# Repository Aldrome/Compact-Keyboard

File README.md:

# Compact Piano Keyboard with DSP and MIDI functions

Schematic link
https://drive.google.com/drive/folders/1MW6RK4cLdNylEYujYAkNW5wjjUnl7ojT?usp=drive_link

Most piano keyboards that musicians use are full scale, which causes problems for composing or playing
in places that lack the space or accessibility, since it is made for performance. This keyboard project has the
focus of minimizing size to something you can fit on a desk and be able to move more freely with it. It will be
more of a MIDI controller and music creation, not as a performance machine.

### Current Objective
	Aldrich: Code general functions and create midi function for 1-3 keys
 	Andrew:  Create a keyboard matrix (48 keys) [Search keyboard matrix for more info]

## Issues to think about:
	- Choosing a microcontroller with the DSP and MIDI capability (Using Teensy 4.1 + Audio Shield Rev D)
	- Handle the keyboard matrix and decide the key amount
	- PCB designing and how to route the I/Os
	- The type of inputs, considering it is a piano

## Planning with steps
	1. Prepare microcontroller for use (solder all pin feet in place)
	2. Test out audio I/O using only the headphones
	3. Prototype a simple synth wave maker using a few buttons
	4. If possible, use a synth wave synthesizer to create a piano sound, maybe more. Else, use audio from free source.
	5. Create a prototype keyboard matrix, and a full scale on KiCad. Also add anti-ghosting using diodes.
	6. Test out potentiometer to divide the input keys to 2 sections.
	7. Add a slider + button for DSP, similar to a mixer.
	8. Depending on the time constraint and resources, print a PCB to handle all these features.

## Additional feature that can be added, though not a priority
	1. A display with UI implementation to decide instrument or maybe change DSP settings.
	2. The input keys by default will be a simple button, similar to a typing keyboard.
	   But if possible, use a sensitivity keyboard using a 2 point detector.
	3. No casings for this project.

Notes: This project will be done in 2 parts for every steps that includes prototyping. One being the physical prototype and
       the other part being the schematic design. After finishing schematic, create a footprint for PCB. Printing a PCB will not
       be a priority, as the demo will mainly be a concept using a prototype. Though we will print a PCB if possible.

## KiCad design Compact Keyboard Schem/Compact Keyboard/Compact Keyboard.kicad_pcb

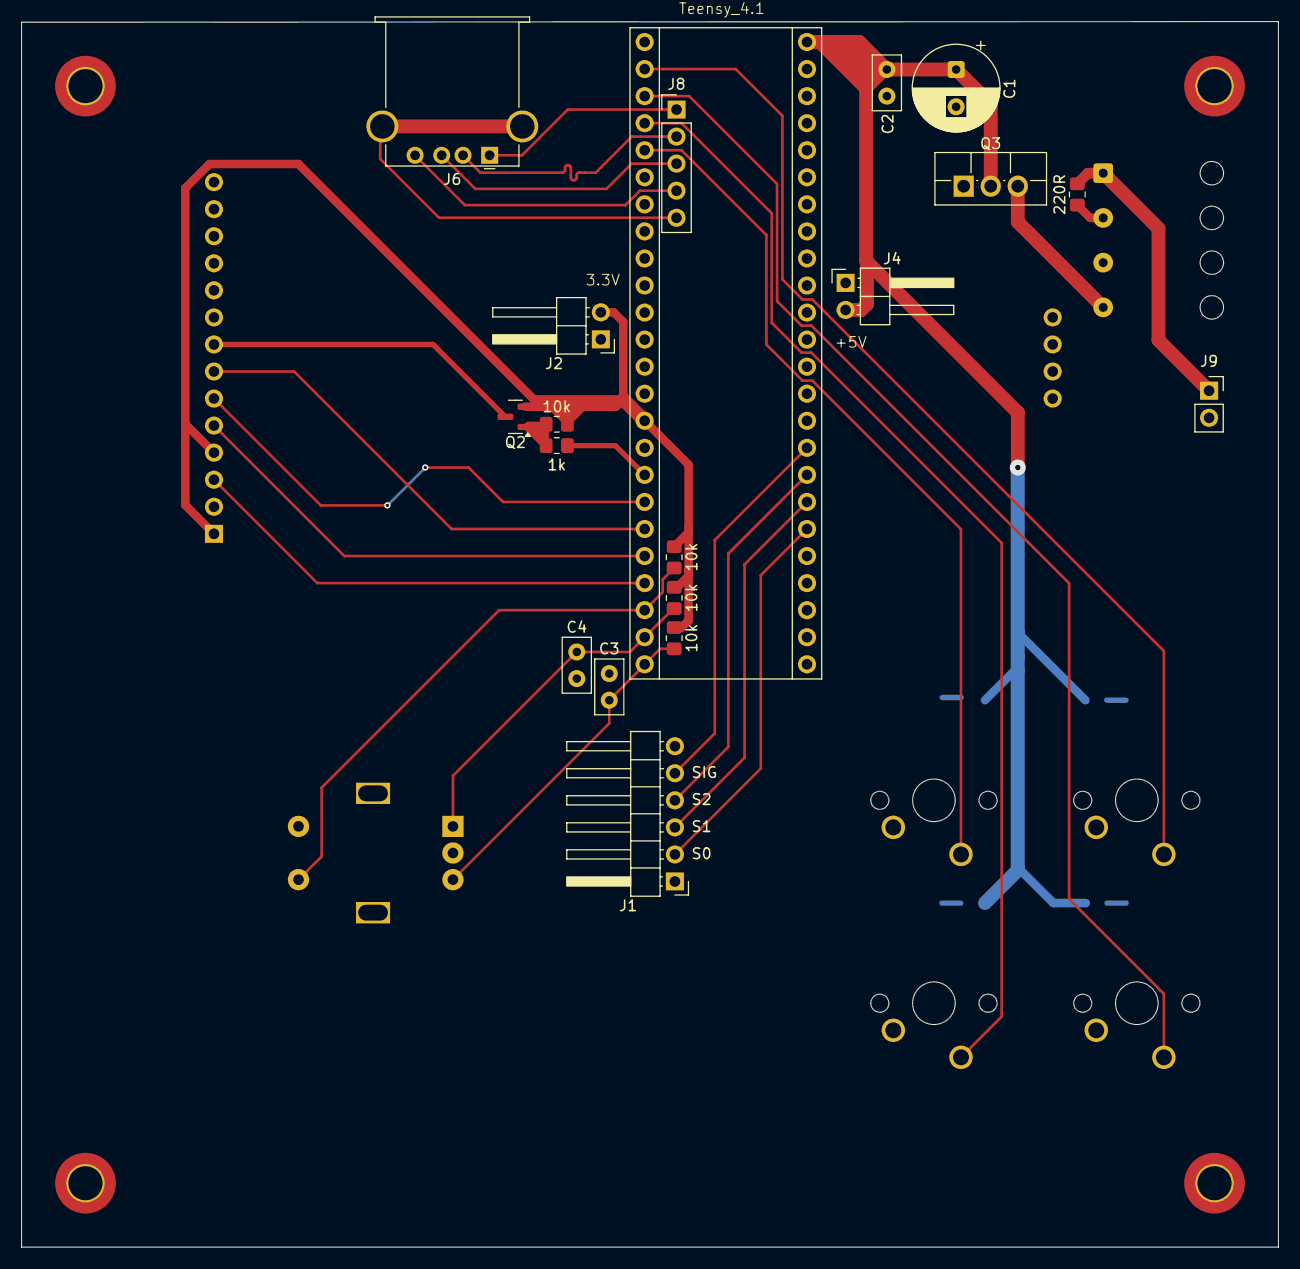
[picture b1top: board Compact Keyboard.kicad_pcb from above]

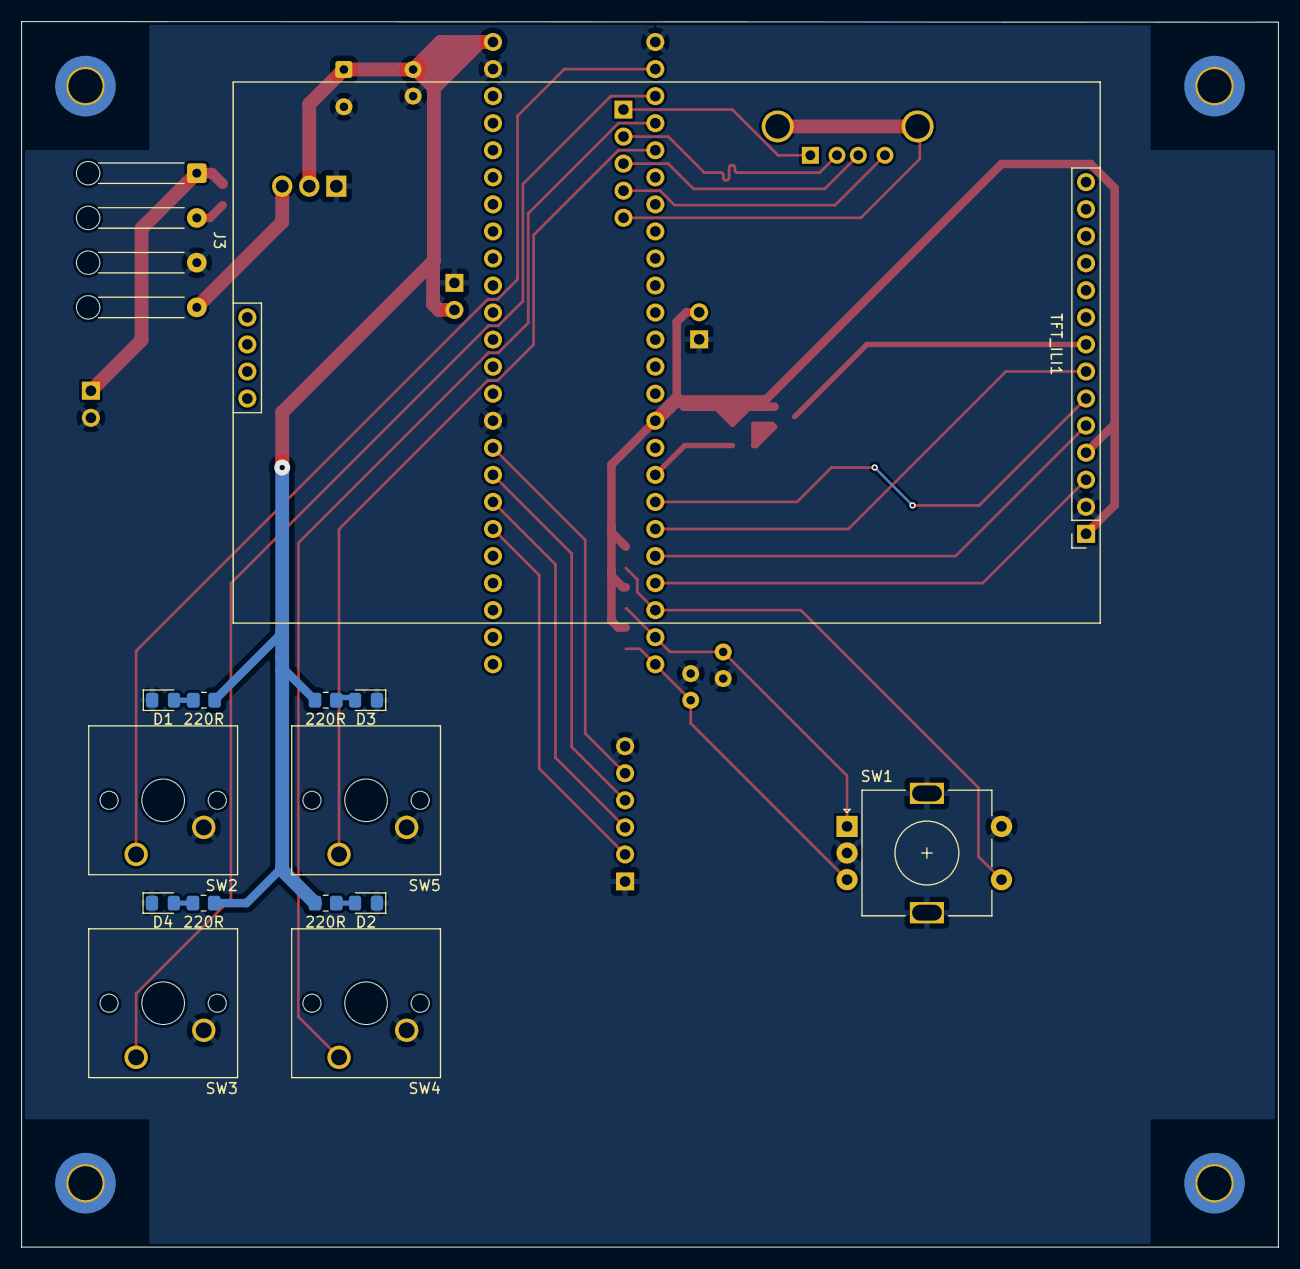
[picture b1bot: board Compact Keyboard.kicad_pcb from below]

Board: 2 copper layers, 118.0 x 115.1 mm, 34 parts (15 on the bottom side), 33 nets.

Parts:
1k: 1k; R_0805_2012Metric_Pad1.20x1.40mm_HandSolder
10k, 10k#2, 10k#4: 10K; R_0805_2012Metric_Pad1.20x1.40mm_HandSolder
10k#3: 10k; R_0805_2012Metric_Pad1.20x1.40mm_HandSolder
220R, 220R#2, 220R#3, 220R#4, 220R#5: 220R; R_0805_2012Metric_Pad1.20x1.40mm_HandSolder
C1: 470uF; CP_Radial_D8.0mm_P3.50mm
C2, C3, C4: 0.1uF; C_Disc_D5.0mm_W2.5mm_P2.50mm
D1, D2, D3, D4: LED; LED_0805_2012Metric_Pad1.15x1.40mm_HandSolder
J1: MUX+POT; PinHeader_1x06_P2.54mm_Horizontal
J2: MUX Power; PinHeader_1x02_P2.54mm_Horizontal
J3: SW_Switch_LED; SolderWire-0.25sqmm_1x04_P4.2mm_D0.65mm_OD1.7mm_Relief
J4: PAM8406 Power; PinHeader_1x02_P2.54mm_Horizontal
J6: USB_A; USB_A_Stewart_SS-52100-001_Horizontal
J8: USB_Host; PinHeader_1x05_P2.54mm_Vertical
J9: Jack-DC; PinSocket_1x02_P2.54mm_Vertical
Q2: Q_PMOS_GSD; SOT-23
Q3: Q_PMOS_GDS; TO-220F-3_Vertical
SW1: RotaryEncoder_Switch_MP; RotaryEncoder_Alps_EC11E-Switch_Vertical_H20mm
SW2, SW3, SW4, SW5: SW_Push; SW_Cherry_MX_1.00u_PCB
TFT_ILI1: ILI9341_TFT
Teensy_4.1: Teensy

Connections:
+3.3V: 10k.1, 10k#2.1, 10k#3.2, 10k#4.2, J2.2, Q2.2 (S), TFT_ILI1.1 (VCC), TFT_ILI1.4 (RESET), Teensy_4.1.15 (3.3V), Teensy_4.1.46 (3.3V)
+5V: 220R#2.2, 220R#3.2, 220R#4.2, 220R#5.2, C1.1, C2.1, J4.2, Q3.2 (D), Teensy_4.1.48 (Vin)
/Buttons/BTN1_IN: SW2.1, Teensy_4.1.2 (0)
/Buttons/BTN2_IN: SW3.1, Teensy_4.1.3 (1)
/Buttons/BTN3_IN: SW4.1, Teensy_4.1.4 (2)
/Buttons/BTN4_IN: SW5.1, Teensy_4.1.5 (3)
/D+_USB: J6.3 (D+), J8.3
/D-_USB: J6.2 (D-), J8.2
/GND_USB: J6.4 (GND), J8.4
/ILI_9341/CS_LCD: TFT_ILI1.3 (CS), Teensy_4.1.21 (29)
/ILI_9341/DC_LCD: TFT_ILI1.5 (DC), Teensy_4.1.20 (28)
/ILI_9341/LED_LCD: 1k.2, Teensy_4.1.17 (25)
/ILI_9341/MOSI_LCD: TFT_ILI1.6 (SDI(MOSI)), Teensy_4.1.18 (26)
/ILI_9341/SCK_LCD: TFT_ILI1.7 (SCK), Teensy_4.1.19 (27)
/Rotary_Encoder/CLK_RE: 10k.2, C3.1, SW1.B, Teensy_4.1.24 (32)
/Rotary_Encoder/DT_RE: 10k#2.2, C4.1, SW1.A, Teensy_4.1.23 (31)
/Rotary_Encoder/SW_RE: 10k#4.1, SW1.S1, Teensy_4.1.22 (30)
/S0_MUX: J1.2, Teensy_4.1.30 (38)
/S1_MUX: J1.3, Teensy_4.1.31 (39)
/S2_MUX: J1.4, Teensy_4.1.32 (40)
/SIG_MUX: J1.5, Teensy_4.1.33 (41)
/Shield_USB: J6.5 (Shield), J8.5
/VBUS_USB: J6.1 (VBUS), J8.1
GND: C1.2, C2.2, C3.2, C4.2, D1.1 (K), D2.1 (K), D3.1 (K), D4.1 (K), J1.1, J1.6, J2.1, J3.3, J4.1, J9.2, Q3.1 (G), SW1.C, SW1.MP, SW1.S2, SW2.2, SW3.2, SW4.2, SW5.2, TFT_ILI1.2 (GND), Teensy_4.1.1 (GND), Teensy_4.1.34 (GND), Teensy_4.1.47 (GND)
unnamed: 220R#4.1, D1.2 (A)
unnamed: 220R#2.1, D2.2 (A)
unnamed: 220R#5.1, D3.2 (A)
unnamed: 220R#3.1, D4.2 (A)
unnamed: 220R.2, J3.1, J9.1
unnamed: 220R.1, J3.2
unnamed: J3.4, Q3.3 (S)
unnamed: Q2.3 (D), TFT_ILI1.8 (LED)
unnamed: 1k.1, 10k#3.1, Q2.1 (G)

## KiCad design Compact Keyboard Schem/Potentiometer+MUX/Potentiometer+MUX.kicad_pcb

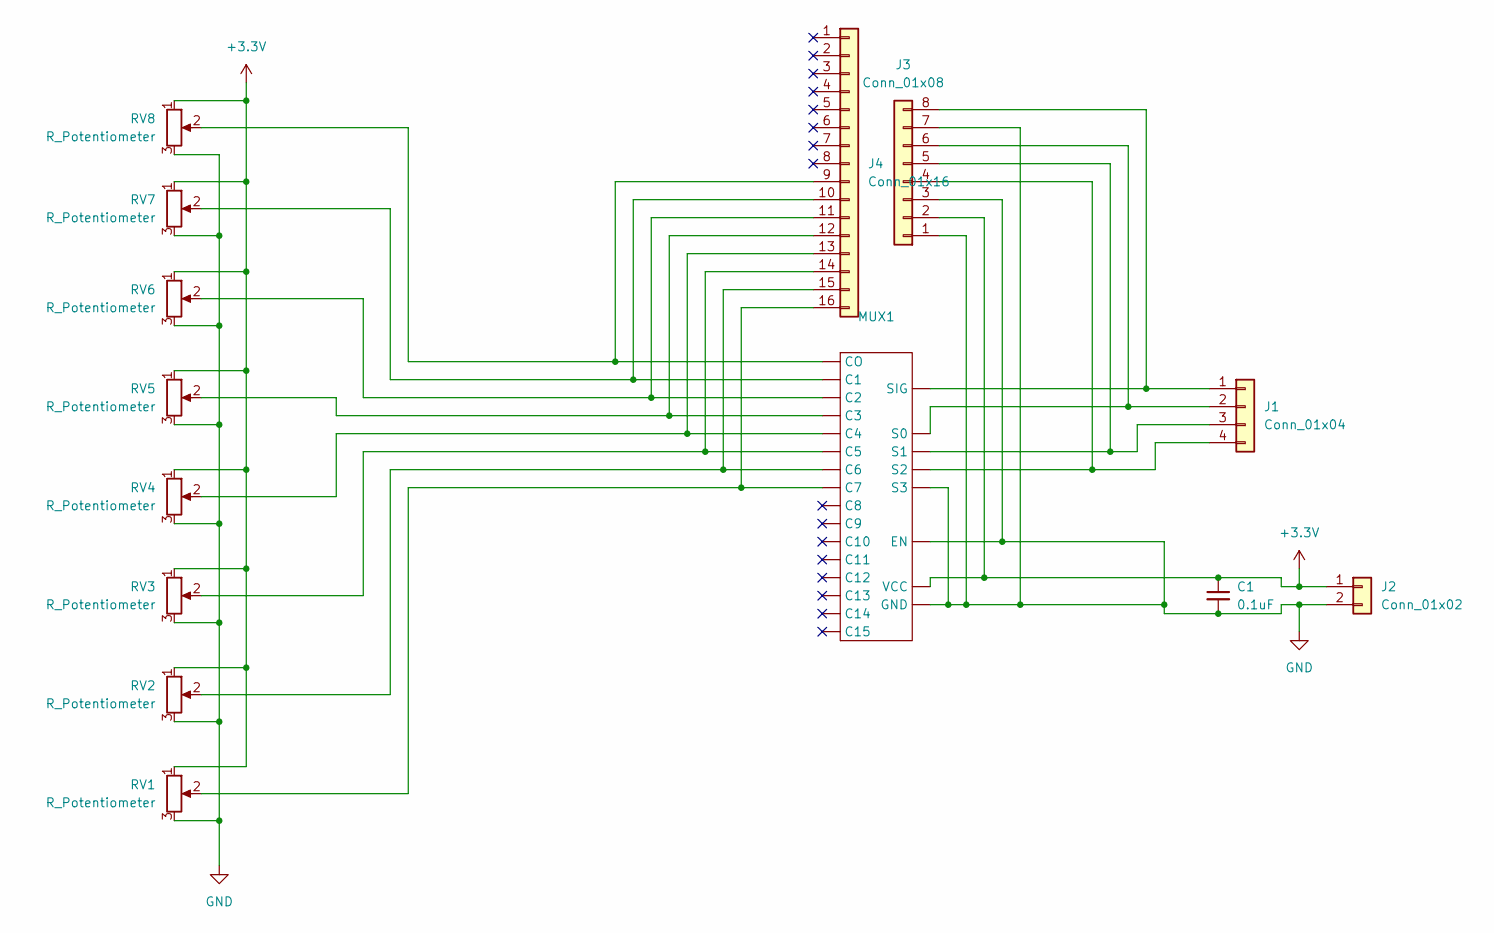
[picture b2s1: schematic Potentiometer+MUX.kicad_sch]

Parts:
C1: 0.1uF; C_Disc_D5.0mm_W2.5mm_P2.50mm
J1: Conn_01x04; PinHeader_1x04_P2.54mm_Horizontal
J2: Conn_01x02; PinHeader_1x02_P2.54mm_Horizontal
J3: Conn_01x08; PinHeader_1x08_P2.54mm_Vertical
J4: Conn_01x16; PinSocket_1x16_P2.54mm_Vertical
MUX1: (no value)
RV1, RV2, RV3, RV4, RV5, RV6, RV7, RV8: R_Potentiometer; Potentiometer_Omeg_PC16BU_Vertical

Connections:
+3.3V: C1.1, J2.1, J3.2, MUX1., RV1.1, RV2.1, RV3.1, RV4.1, RV5.1, RV6.1, RV7.1, RV8.1
GND: C1.2, J2.2, J3.1, J3.3, J3.7, MUX1., RV1.3, RV2.3, RV3.3, RV4.3, RV5.3, RV6.3, RV7.3, RV8.3
unnamed: J1.1, J3.8, MUX1.
unnamed: J1.2, J3.6, MUX1.
unnamed: J1.3, J3.5, MUX1.
unnamed: J1.4, J3.4, MUX1.
unnamed: J4.9, MUX1., RV8.2
unnamed: J4.10, MUX1., RV7.2
unnamed: J4.11, MUX1., RV6.2
unnamed: J4.12, MUX1., RV5.2
unnamed: J4.13, MUX1., RV4.2
unnamed: J4.14, MUX1., RV3.2
unnamed: J4.15, MUX1., RV2.2
unnamed: J4.16, MUX1., RV1.2

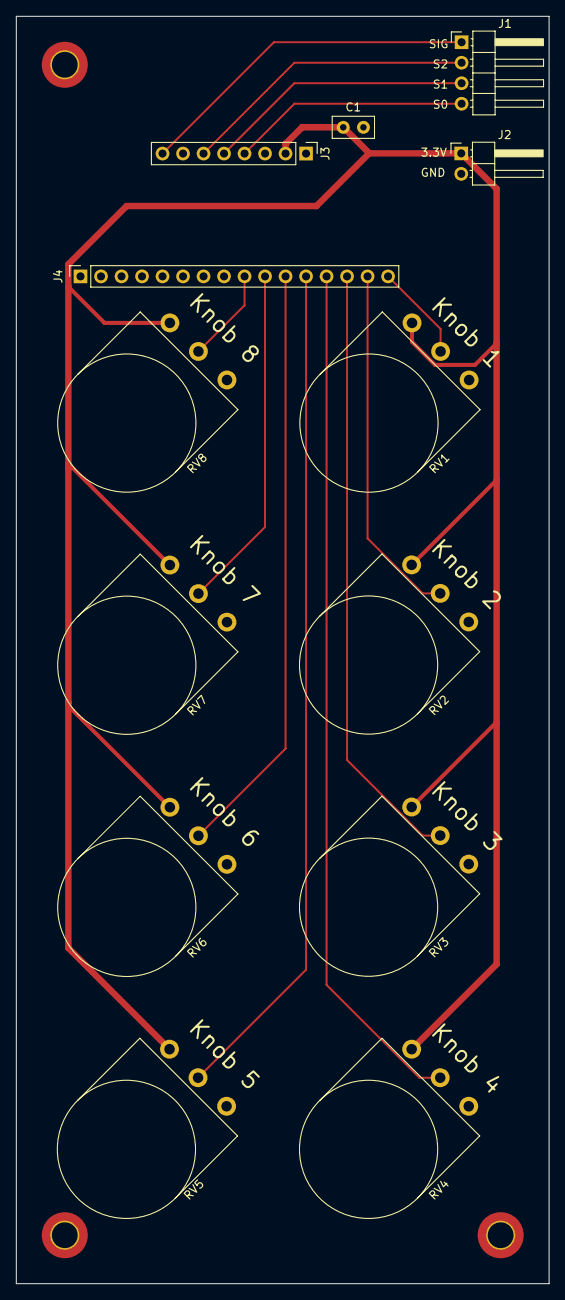
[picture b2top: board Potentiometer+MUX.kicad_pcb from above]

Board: 2 copper layers, 66.0 x 157.0 mm, 13 parts (0 on the bottom side), 14 nets.

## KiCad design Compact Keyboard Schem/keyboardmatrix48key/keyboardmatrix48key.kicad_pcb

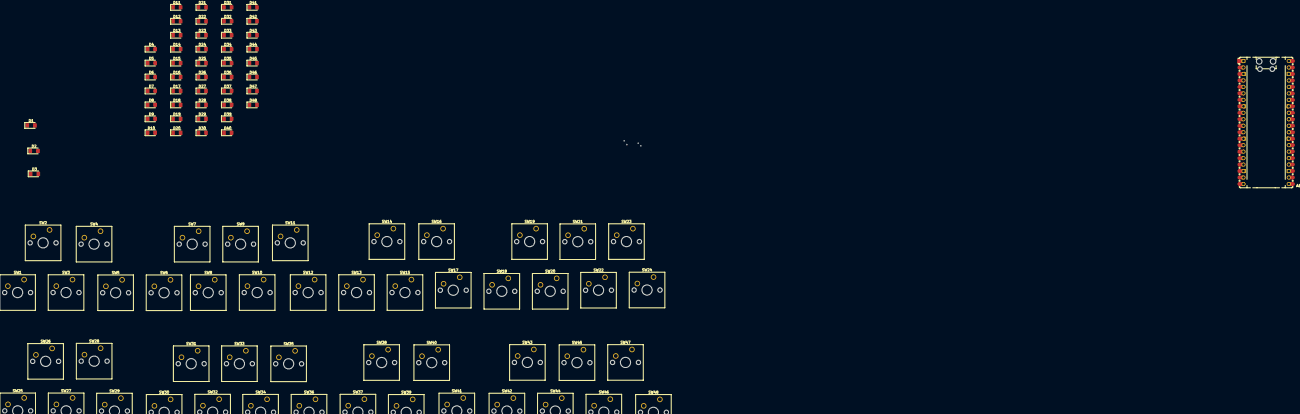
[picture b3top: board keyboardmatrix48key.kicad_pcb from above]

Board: 2 copper layers, 97 parts (0 on the bottom side), 52 nets, no tracks yet.

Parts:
A1: RaspberryPi_Pico; RaspberryPi_Pico_Common_Unspecified
D1, D2, D3, D4, D5, D6, D7, D8, D9, D10, D11, D12, D13, D14, D15, D16, D17, D18, D19, D20, D21, D22, D23, D24, D25, D26, D27, D28, D29, D30, D31, D32, D33, D34, D35, D36, D37, D38, D39, D40, D41, D42, D43, D44, D45, D46, D47, D48: D; D_1206_3216Metric_Pad1.42x1.75mm_HandSolder
SW1, SW2, SW3, SW4, SW5, SW6, SW7, SW8, SW9, SW10, SW11, SW12, SW13, SW14, SW15, SW16, SW17, SW18, SW19, SW20, SW21, SW22, SW23, SW24, SW25, SW26, SW27, SW28, SW29, SW30, SW31, SW32, SW33, SW34, SW35, SW36, SW37, SW38, SW39, SW40, SW41, SW42, SW43, SW44, SW45, SW46, SW47, SW48: SW_Push; SW_Cherry_MX_1.00u_PCB

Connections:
/COL1: A1.2 (GPIO1), A1.4 (GPIO2), A1.5 (GPIO3), A1.6 (GPIO4), A1.7 (GPIO5), A1.9 (GPIO6), A1.10 (GPIO7), A1.11 (GPIO8), A1.12 (GPIO9), A1.14 (GPIO10), A1.15 (GPIO11), A1.16 (GPIO12), D2.1 (K), D3.1 (K), D4.1 (K), D5.1 (K), D6.1 (K), D8.1 (K), D9.1 (K), D10.1 (K), D11.1 (K), D12.1 (K), D14.1 (K), D15.1 (K), D16.1 (K), D17.1 (K), D18.1 (K), D20.1 (K), D21.1 (K), D22.1 (K), D23.1 (K), D24.1 (K), D26.1 (K), D27.1 (K), D28.1 (K), D29.1 (K), D30.1 (K), D32.1 (K), D33.1 (K), D34.1 (K), D35.1 (K), D36.1 (K), D38.1 (K), D39.1 (K), D40.1 (K), D41.1 (K), D42.1 (K), D44.1 (K), D45.1 (K), D46.1 (K), D47.1 (K), D48.1 (K), SW1.2, SW2.2, SW3.2, SW4.2, SW5.2, SW6.2, SW7.2, SW9.2, SW10.2, SW11.2, SW12.2, SW13.2, SW14.2, SW15.2, SW17.2, SW18.2, SW19.2, SW20.2, SW21.2, SW22.2, SW23.2, SW25.2, SW26.2, SW27.2, SW28.2, SW29.2, SW30.2, SW31.2, SW33.2, SW34.2, SW35.2, SW36.2, SW37.2, SW38.2, SW39.2, SW41.2, SW42.2, SW43.2, SW44.2, SW45.2, SW46.2, SW47.2
/COL8: A1.17 (GPIO13), SW8.2, SW16.2, SW24.2, SW32.2, SW40.2, SW48.2
/ROW1: A1.1 (GPIO0), D1.1 (K), D7.1 (K), D13.1 (K), D19.1 (K), D25.1 (K), D31.1 (K), D37.1 (K), D43.1 (K)
unnamed: A1.3 (GND), A1.8 (GND), A1.13 (GND), A1.18 (GND), A1.23 (GND), A1.28 (GND), A1.38 (GND)
unnamed: D1.2 (A), SW1.1
unnamed: D2.2 (A), SW9.1
unnamed: D3.2 (A), SW17.1
unnamed: D4.2 (A), SW25.1
unnamed: D5.2 (A), SW33.1
unnamed: D6.2 (A), SW41.1
unnamed: D7.2 (A), SW2.1
unnamed: D8.2 (A), SW10.1
unnamed: D9.2 (A), SW18.1
unnamed: D10.2 (A), SW26.1
unnamed: D11.2 (A), SW34.1
unnamed: D12.2 (A), SW42.1
unnamed: D13.2 (A), SW3.1
unnamed: D14.2 (A), SW11.1
unnamed: D15.2 (A), SW19.1
unnamed: D16.2 (A), SW27.1
unnamed: D17.2 (A), SW35.1
unnamed: D18.2 (A), SW43.1
unnamed: D19.2 (A), SW4.1
unnamed: D20.2 (A), SW12.1
unnamed: D21.2 (A), SW20.1
unnamed: D22.2 (A), SW28.1
unnamed: D23.2 (A), SW36.1
unnamed: D24.2 (A), SW44.1
unnamed: D25.2 (A), SW5.1
unnamed: D26.2 (A), SW13.1
unnamed: D27.2 (A), SW21.1
unnamed: D28.2 (A), SW29.1
unnamed: D29.2 (A), SW37.1
unnamed: D30.2 (A), SW45.1
unnamed: D31.2 (A), SW6.1
unnamed: D32.2 (A), SW14.1
unnamed: D33.2 (A), SW22.1
unnamed: D34.2 (A), SW30.1
unnamed: D35.2 (A), SW38.1
unnamed: D36.2 (A), SW46.1
unnamed: D37.2 (A), SW7.1
unnamed: D38.2 (A), SW15.1
unnamed: D39.2 (A), SW23.1
unnamed: D40.2 (A), SW31.1
unnamed: D41.2 (A), SW39.1
unnamed: D42.2 (A), SW47.1
unnamed: D43.2 (A), SW8.1
unnamed: D44.2 (A), SW16.1
unnamed: D45.2 (A), SW24.1
unnamed: D46.2 (A), SW32.1
unnamed: D47.2 (A), SW40.1
unnamed: D48.2 (A), SW48.1

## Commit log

2025-09-06 Starting out
2025-09-18 Symbol file for Teensy 4.1 + Audio Shield Rev D
2025-11-22 Add schematic link to README
    Added schematic link for the Compact Piano Keyboard project.
2025-11-22 Add Teensy 4.1 code
2025-11-22 Add README with compilation notes and library info
    Added usage notes and library requirements for the project.
2025-11-22 Format README with Markdown headers and code blocks
2025-11-22 Update README to include USB Type information
    Added USB Type section to README with Serial, MIDI, and Audio.
2025-12-08 Added MUX for pot handling
2025-12-13 Potentiometer+MUX
2025-12-17 PAM8403 Amplifier
2025-12-17 Rotary Encoder
2026-02-26 Layout + Schem Update
2026-02-26 Finished Layout
2026-02-27 Smaller MUX, Main Board design
2026-02-27 More Inputs for Teensy
2026-03-01 keyboardmatrix48key
2026-03-05 Cleaned Up Space
2026-03-05 2nd Move
2026-03-11 Post PCB Manufacturing
    Specifically the Potentiometer+ MUX
2026-03-19 Pushing Update
    Latest version after PCB printing
